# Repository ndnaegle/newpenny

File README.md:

# newpenny
This is an Arduino Shield to interface an Arduino to a souvenir making machine.  

The shield contains signal conditioning to give the Arduino more ESD protection as a controller  for the penny press.  

The shield also contains an output level shifter to allow the Arduino to control solid-state relays  that require 12V control inputs.  

The shield also contains a 128x64 pixel display as a debugging aid, and a non-volatile serial memory for storing operational and debug data.  

The shield could serve as a general-purpose I/O conditioning module along with non-volatile memory that could allow the Arduino to retain its
operational state through power failures, by means of appropriate software.

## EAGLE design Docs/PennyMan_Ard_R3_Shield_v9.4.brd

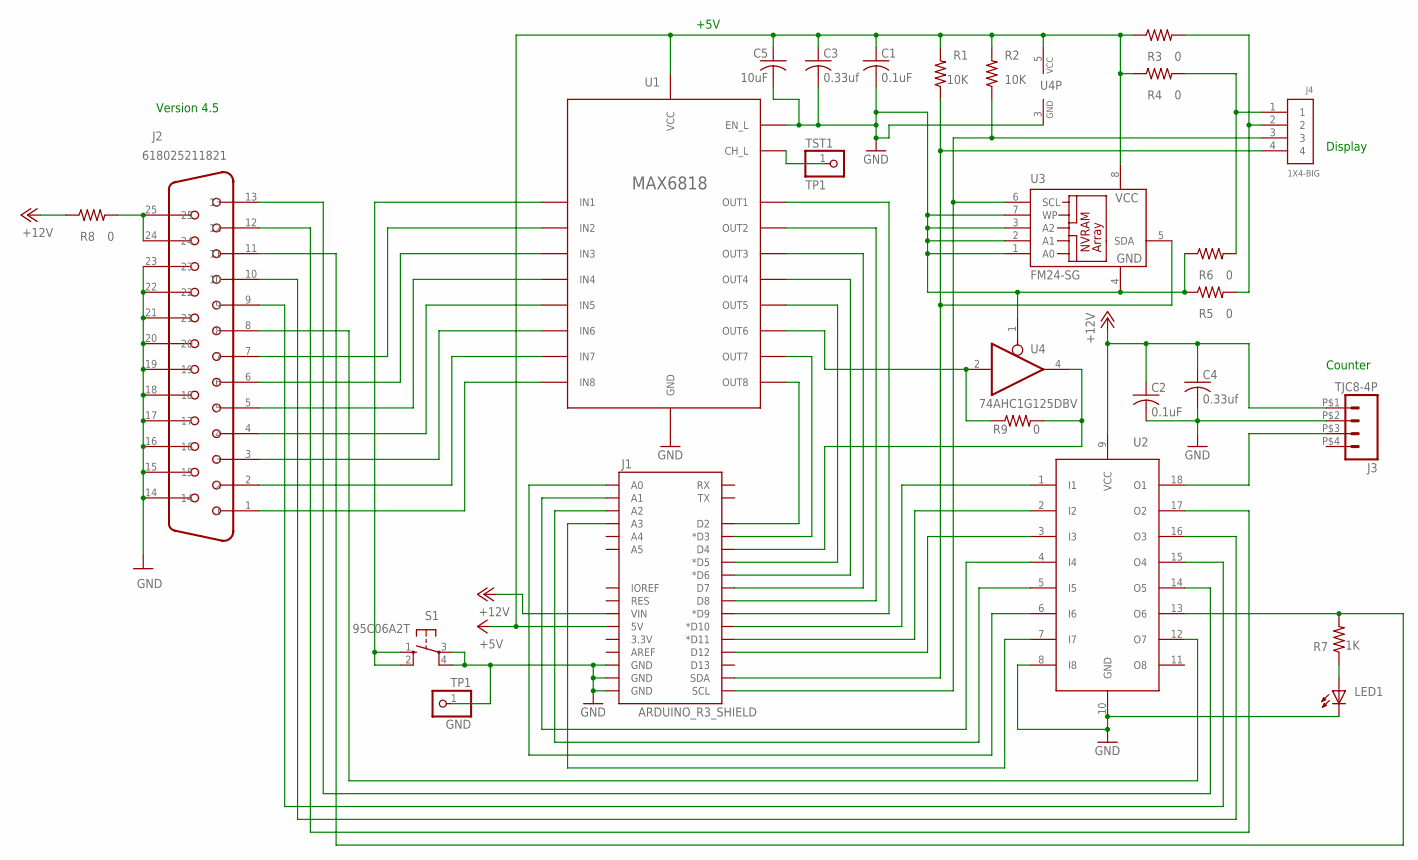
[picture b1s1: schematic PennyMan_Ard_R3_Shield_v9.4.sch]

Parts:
C1, C2: 0.1uF; C0805
C3, C4: 0.33uf; C1206
C5: 10uF; C1812
GND: TP1; 1X01
J1: ARDUINO_R3_SHIELD; UNO_R3_SHIELD
J2: 618025211821
J3: TJC8-4P
J4: 1X4-BIG; 1X04-BIG
LED1: LEDSML0805; SML0805
R1, R2: 10K; R0805
R3, R4, R5, R6, R8, R9: 0; R0805
R7: 1K; R0805
S1: 95C06A2T; B3F-10XX
TST1: TP1; 1X01
U1: MAX6818; SSOP20
U2: TD62783AG; SOP18
U3: FM24-SG; SO8
U4: 74AHC1G125DBV; SOT23-5

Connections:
+5V: C1.1, C3.1, C5.1, J1.5V, R1.2, R2.2, R3.1, R4.1, U1.VCC, U3.8 (VCC), U4.5 (VCC)
+12V: C2.1, C4.1, J1.VIN, J3.P$1 (1), R8.1, U2.9 (VCC)
GND: C1.2, C2.2, C3.2, C4.2, C5.2, GND.1, J1.GND@0 (GND), J1.GND@1 (GND), J1.GND@2 (GND), J2.14, J2.15, J2.16, J2.17, J2.18, J2.19, J2.20, J2.21, J2.22, J2.23, J3.P$2 (2), LED1.C, R5.1, R6.1, S1.3, S1.4 (P1), U1.EN_L, U1.GND, U2.8 (I8), U2.10 (GND), U3.1 (A0), U3.2 (A1), U3.3 (A2), U3.4 (GND), U3.7 (WP), U4.1 (OE), U4.3 (GND)
unnamed: J2.1, U1.IN8
unnamed: J2.2, U1.IN7
unnamed: J2.3, U1.IN6
unnamed: J2.4, U1.IN5
unnamed: J2.5, U1.IN4
unnamed: J2.6, U1.IN3
unnamed: J2.7, U1.IN2
unnamed: J1.D9 (*D9), U1.OUT1
unnamed: J1.D8, U1.OUT2
unnamed: J1.D7, U1.OUT3
unnamed: J1.D6 (*D6), U1.OUT4
unnamed: J1.D5 (*D5), U1.OUT5
unnamed: J1.D3 (*D3), U1.OUT7
unnamed: J3.P$3 (3), U2.18 (O1)
unnamed: J1.D2, U1.OUT8
unnamed: J1.A0, U2.6 (I6)
unnamed: J1.D10 (*D10), U2.1 (I1)
unnamed: J1.D11 (*D11), U2.2 (I2)
unnamed: J1.D12, U2.3 (I3)
unnamed: J1.A1, U2.4 (I4)
unnamed: J2.12, U2.17 (O2)
unnamed: J2.10, U2.16 (O3)
unnamed: J2.9, U2.15 (O4)
unnamed: TST1.1, U1.CH_L
unnamed: J1.SCL, J4.3, R2.1, U3.6 (SCL)
unnamed: J2.13, U2.14 (O5)
unnamed: J4.1, R4.2, R6.2
unnamed: J1.SDA, J4.4, R1.1, U3.5 (SDA)
unnamed: J4.2, R3.2, R5.2
unnamed: J1.D4, R9.2, U4.4 (O)
unnamed: J1.A2, U2.5 (I5)
unnamed: LED1.A, R7.1
unnamed: J2.11, R7.2, U2.13 (O6)
unnamed: S1.1 (S), S1.2 (S1), U1.IN1
unnamed: J1.A3, U2.7 (I7)
unnamed: J2.8, U2.12 (O7)
unnamed: J2.24, J2.25, R8.2
unnamed: R9.1, U1.OUT6, U4.2 (I)

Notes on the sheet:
+5V
Version 4.5
Counter
Display

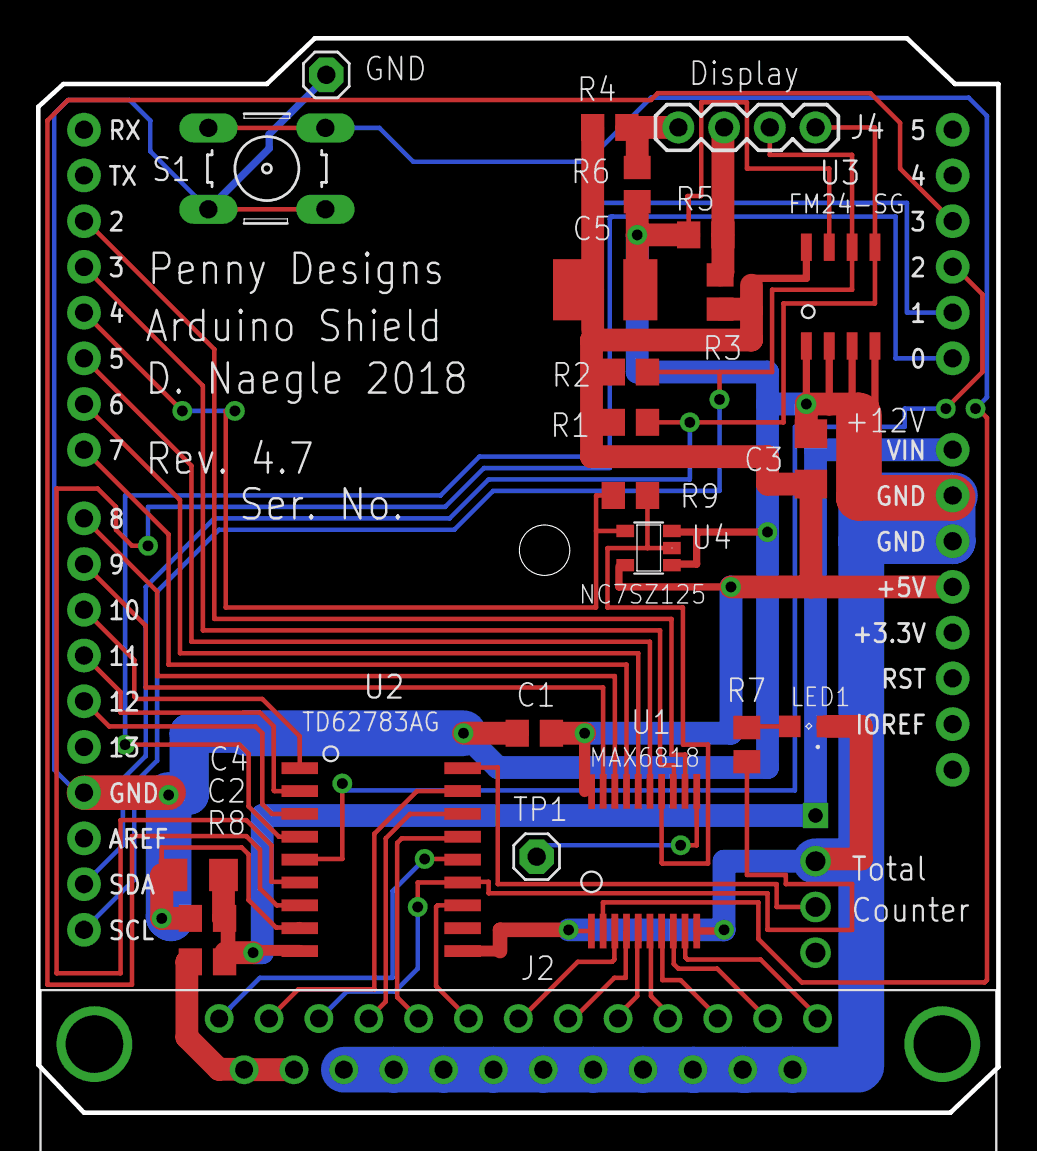
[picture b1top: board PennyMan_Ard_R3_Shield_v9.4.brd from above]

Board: 2 copper layers, 53.3 x 59.7 mm, 26 parts (0 on the bottom side), 41 nets.

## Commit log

2017-06-24 File not needed.
2017-06-24 Blink easy demo for Arduino
2017-06-24 blinking digit patterns
2017-06-24 prints to serial
2017-06-25 first pass at input and output pin definitions
2017-06-25 Code cleanup
2017-06-25 forgot to save some changes
2017-07-10 first working version
2017-07-20 Updated library names and serial speed
2017-07-22 Updates for new shield
2017-07-24 Initial FRAM support
2017-07-25 Improved FRAM logging
2019-01-06 Put debug code back in and moving changes from Jon's repo
2019-01-21 Corrected/Completed pinout
    Corrected and completed the DB25 connector pin-out, including generic (unused) outputs
2022-03-10 Add files via upload
    STL file for 3D printing a holder for the Arduino and shield for the PennyMan project.
2022-03-12 Add files via upload
    Added latest version of Eagle schematic and board layout files, Bill of Materials, and Zip archive of all manufacturing files (Gerbers, etc.)
2022-03-12 Add files via upload
    Datasheets for ICs
2022-03-12 Add files via upload
    (not so) Optional display module. Note that the design accommodates either VCC as left-most pin (stuff R4, R5) or GND as left-most pin (stuff R3, R6). This image shows GND on the left-most pin.
2022-03-12 Add files via upload
    First uploaded version of documentation of the Shield board, along with random thoughts on operation and testing of the Shield. Written by David Naegle.
2022-03-12 Add files via upload
    Older versions of schematic and layout files. Note: earlier versions used the MAX chip for debouncing, but it never worked.
2022-03-12 Add files via upload
    Latest Shield layout. (This is labeled Ver 4.9 on silkscreen; the latest version that was actually manufactured is Ver 4.8 on the silkscreen).
2022-03-12 Add files via upload
    STL file for mounting Arduino.
2022-03-12 Add files via upload
    additional documentation, and some explorations for a coin-accept latch mechanism that doesn't require continuous power to a solenoid to keep the machine in a coin-accepting state.
2022-03-12 Create README.md
    Initial version
2022-03-12 Delete Coin-Accept 4-Bar Latch Mechanism.svg
    this file should have been added to the Docs folder. Delete it from top level.
2022-03-12 Delete Coin-Accept Latch Mechanism.svg
    This should have been added to the Docs folder. Delete it from top level.
2022-03-12 Delete PennyMan_Ard_R3_Shield_v9.5_all_layers.jpg
    erroneously added to top level; should be in Docs directory.
2022-03-12 Delete PennyMan_Ard_R3_Shield_v9.5_schematic.jpg
    erroneously added at top level; should be put in Docs folder.
2022-03-12 Delete PennyMan_Ard_R3_Shield_v9.5print.pdf
    erroneously added at top level; this file has been added to Docs folder.

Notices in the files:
parts and their libraries:
SparkFun-Boards: Licensing: Creative Commons ShareAlike 4.0 International - https://creativecommons.org/licenses/by-sa/4.0
EagleLibrary_Wuerth_Elektronik_eiCan_Com: Copyright: Würth Elektronik
